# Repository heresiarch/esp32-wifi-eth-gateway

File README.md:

# esp32-wifi-eth-gateway
Proof-of-concept Wifi ⇄ Ethernet gateway running on an ESP32-C6.

## Hardware
- Waveshare ESP32-C6-Zero (or compatible ESP32-C6)
- WIZnet W5500 SPI Ethernet module (or compatible SPI Ethernet adapter)

## Project summary
This project implements a network gateway that forwards traffic between the ESP32's Wi‑Fi interface and a SPI‑based Ethernet interface. It can be used to bridge devices on an Ethernet subnet onto a Wi‑Fi network (or vice versa) for testing, prototyping, and embedded networking research. The implementation uses ESP-IDF networking components and the W5500 driver included as a component.

## Features
- Bridge packets between Wi‑Fi and Ethernet interfaces
- Uses ESP‑IDF networking stack
- Configurable via `menuconfig` / `sdkconfig`
- Example application code in `main/` (`main.c`, `proxy.c`)
- Wifi runs as DHCP client
- Ethernet run as DHCP Server
- TCP proxy on port 8888, plus an optional second independent proxy (default port 502 for Modbus TCP) that can be switched on or off with `SECOND_PROXY_ENABLE`, each with its own target

## Repository layout
- `main/` — application source and component Kconfig
- `partition_table/`, `sdkconfig*` — project configuration
- `managed_components/` — included external components (W5500, ethernet init, etc.)
- `build/` — build output (ignored by source control)
- `circuit-design` KiCad 9 project

## Requirements
- ESP-IDF (supported version: refer to the `esp-idf/` subfolder or `CMakeLists.txt`)
- A toolchain for the target (e.g. for ESP32‑C6)
- `idf.py` (part of ESP‑IDF)

## Quick build & flash
1. Set up ESP‑IDF and toolchain, then source the environment (example):

```bash
. $HOME/esp/esp-idf/export.sh
```

2. (Optional) set the target if needed:

```bash
idf.py set-target esp32c6
```

3. Create `main/Kconfig.projbuild` from the template (see "Create your own configuration") and configure project options (wifi credentials, ethernet pins, etc.):

```bash
idf.py menuconfig
```

4. Build, flash and monitor:

```bash
idf.py build
idf.py -p /dev/ttyUSB0 flash monitor
```

Replace `/dev/ttyUSB0` with your serial device.

## Create your own configuration
The project settings (Wi-Fi credentials, Ethernet addressing, proxy ports and targets) are defined in `main/Kconfig.projbuild`. That file is listed in `.gitignore`, so your credentials stay out of the repository. The repository only contains the template `main/Kconfig.projbuild.example`. Before the first build, create your own file from it:

1. Copy the template:

```bash
cp main/Kconfig.projbuild.example main/Kconfig.projbuild
```

2. (Optional) edit the `default` values in `main/Kconfig.projbuild`, for example `WIFI_SSID`, `WIFI_PASSWORD`, `ETHERNET_IP` and the proxy targets. You can also leave the defaults and set everything in step 3.

3. Open menuconfig and check or change the values under "Project Network Configuration":

```bash
idf.py menuconfig
```

   - "Wi-Fi Settings": `WIFI_SSID`, `WIFI_PASSWORD`
   - "Ethernet & Proxy Settings": Ethernet IP, netmask and gateway, the first proxy, and the optional second proxy (`SECOND_PROXY_ENABLE`)

4. Build and flash as described in "Quick build & flash".

Notes:
- Without `main/Kconfig.projbuild` the `CONFIG_*` options used by `main.c` are missing and the build fails.
- Values you set in menuconfig are stored in `sdkconfig`, which takes priority over the `default` values in `Kconfig.projbuild`. If you change a `default` later and the old value is still used, change it in menuconfig, or delete `sdkconfig` and run `idf.py reconfigure`. Note that deleting `sdkconfig` resets all of your settings.
- If you add or rename options in `main/Kconfig.projbuild`, run `idf.py reconfigure` so `sdkconfig` picks them up.
- When the template changes in the repository (new options), compare it with your copy, for example with `diff main/Kconfig.projbuild.example main/Kconfig.projbuild`, and add the new options to your file.
- Do not commit `main/Kconfig.projbuild` or `sdkconfig` if they contain real passwords.

## Configuration notes
- Wi‑Fi credentials and runtime options can be set in `menuconfig` or stored in `sdkconfig`/`sdkconfig.defaults` depending on how the project exposes them.
- Hardware pin mappings for the SPI Ethernet module are configured in `menuconfig` or in the ethernet component source — check `managed_components/espressif__w5500/` for driver-specific settings.

## Proxy configuration
The firmware runs two independent TCP proxy instances. Each one listens on its own port and forwards traffic to its own target. Both are set in `idf.py menuconfig` under "Ethernet & Proxy Settings":

| Option | Default | Purpose |
|---|---|---|
| `SERVER_LISTEN_PORT` | 8888 | Listen port of the first proxy |
| `PROXY_TARGET_ADDRESS` | 10.0.0.2 | Target IP or host of the first proxy |
| `PROXY_TARGET_PORT` | 8888 | Target port of the first proxy |
| `SECOND_PROXY_ENABLE` | y | Switch that enables the second proxy |
| `SECOND_SERVER_LISTEN_PORT` | 502 | Listen port of the second proxy (Modbus TCP) |
| `SECOND_PROXY_TARGET_ADDRESS` | 10.0.0.2 | Target IP or host of the second proxy |
| `SECOND_PROXY_TARGET_PORT` | 502 | Target port of the second proxy |

Notes:
- The second proxy is optional. `SECOND_PROXY_ENABLE` defaults to `y`. The three options `SECOND_SERVER_LISTEN_PORT` (502), `SECOND_PROXY_TARGET_ADDRESS` (10.0.0.2) and `SECOND_PROXY_TARGET_PORT` (502) are visible in `menuconfig` only when the switch is set. When it is unset, only the first proxy is started and the second-port checks are skipped.
- Ports must be in the range 1 to 65535.
- The two listen ports must differ. With `SECOND_PROXY_ENABLE` set, the build fails with a compile-time error if they are equal or out of range. With it unset, only the first port is checked.
- Each proxy serves one client at a time. The two proxies run in parallel and do not affect each other.
- Log lines are prefixed with `[port N]` so you can tell the two proxies apart.
- `main/Kconfig.projbuild.example` is a template with placeholder values. See "Create your own configuration" for how to copy it to `main/Kconfig.projbuild`.

## Wiring (ESP32 → W5500)
Below are the SPI pin assignments used in this project.

| Signal | ESP32-C6 pin | W5500 pin | Direction | Kconfig option |
|---|---|---|---|---|
| SCLK | GPIO4 | SCLK | ESP32 → W5500 | `CONFIG_ETHERNET_SPI_SCLK_GPIO=4` |
| MOSI | GPIO5 | MOSI | ESP32 → W5500 | `CONFIG_ETHERNET_SPI_MOSI_GPIO=5` |
| MISO | GPIO2 | MISO | W5500 → ESP32 | `CONFIG_ETHERNET_SPI_MISO_GPIO=2` |
| CS (CS0) | GPIO3 | SCS | ESP32 → W5500 | `CONFIG_ETHERNET_SPI_CS0_GPIO=3` |
| INT | GPIO15 | INT | W5500 → ESP32 | `CONFIG_ETHERNET_SPI_INT0_GPIO=15` |
| PHY_RST | GPIO14 | RESET | ESP32 → W5500 | `CONFIG_ETHERNET_SPI_PHY_RST0_GPIO=14` |

**Architecture**

- **Overview:** The ESP32 runs a small application that bridges packets between the Wi‑Fi stack (`esp_wifi` / `lwIP`) and a SPI Ethernet controller (W5500). The user-space TCP proxy (`proxy.c`) accepts connections on the ESP32 and forwards bytes between the two interfaces.

- **Responsibilities:**
	- `main.c` — initialises Wi‑Fi, Ethernet and starts the first proxy instance and, if `SECOND_PROXY_ENABLE` is set, the second one.
	- `proxy.c` — accepts TCP connections and forwards traffic between endpoints. `proxy_start()` is called once per enabled port.
	- `status_led.c` — indicates general on status and traffic activity (Ethernet/Wi‑Fi).

Architecture diagram:

```mermaid
flowchart TD
    WIFI(["Wi-Fi network"])
    DEV(["Local devices"])
    W5500["W5500 Ethernet controller"]

    subgraph ESP["ESP32-C6"]
        STA["esp_wifi STA<br/>DHCP client"]
        P1["proxy.c: port 8888<br/>task + buffer"]
        P2["proxy.c: port 502<br/>task + buffer, optional"]
        ETH["esp_eth SPI driver"]
        DHCPS["DHCP server"]
        LED["status_led.c"]
    end

    WIFI <--> STA
    STA <--> P1
    STA <--> P2
    P1 <--> ETH
    P2 <--> ETH
    DHCPS --- ETH
    ETH <-->|SPI| W5500
    W5500 <--> DEV
```

Note: If you change these pins via `menuconfig`, update `sdkconfig` and re-flash the firmware so the driver uses the new assignments.

## Circuit Design
I create a KiCad 9 project with some custom footprints for the following components I used `circuit-design`:
* Waveshare ESP32-C6-Zero with headers
* TPS2553 USB eFuse on DIP-6 Adapter (Powerlimit 400mA)
* Wiznet 5500 module with headers
* generic USB-C Header which included termination resistors

## License & contributors
See the `LICENSE` file for license details. Contributions and issues are welcome.

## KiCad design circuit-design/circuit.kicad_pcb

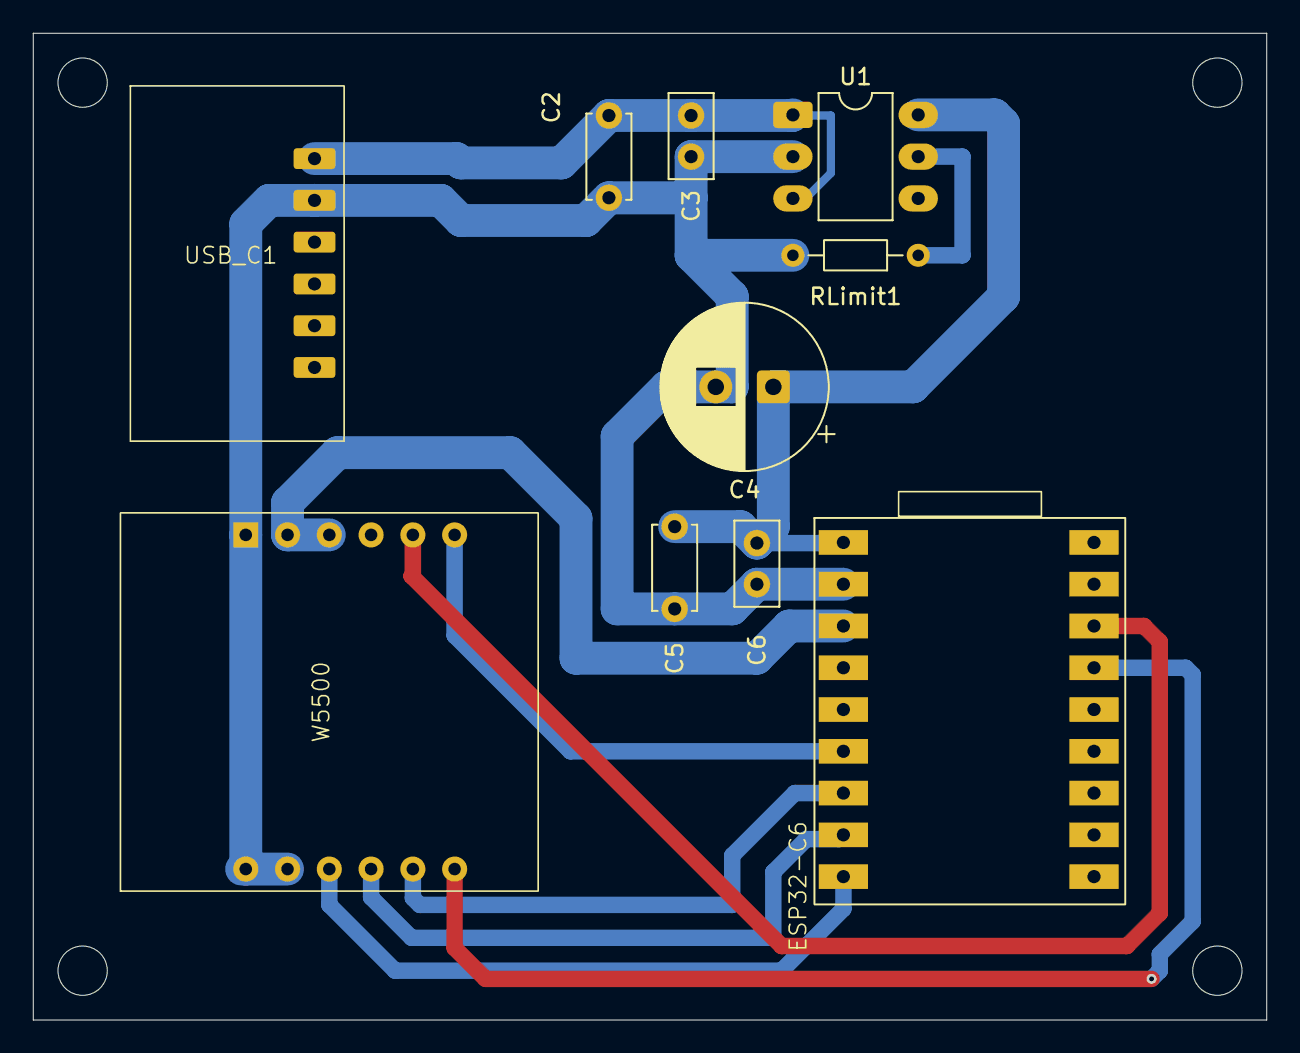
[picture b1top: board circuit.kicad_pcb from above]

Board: 2 copper layers, 75.0 x 60.0 mm, 10 parts (0 on the bottom side), 11 nets.

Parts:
C2, C5: 1uF/10V; C_Disc_D5.0mm_W2.5mm_P5.00mm
C3, C6: 100nF; C_Disc_D5.0mm_W2.5mm_P2.50mm
C4: 1000uF/10V; CP_Radial_D10.0mm_P3.50mm
ESP32-C6: Waveshare-ESP32-C6-Zero
RLimit1: 67k; R_Axial_DIN0204_L3.6mm_D1.6mm_P7.62mm_Horizontal
U1: TPS2553; DIP-6_W7.62mm_LongPads
USB_C1: USB-C-Plug
W5500: w5500-eth-breakout

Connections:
GND: C2.2, C3.2, C4.2, C5.2, C6.2, ESP32-C6.2 (GND), RLimit1.2, U1.2 (GND), USB_C1.2 (GND), W5500.1 (GND), W5500.2 (GND), W5500.12 (GND)
INTn: ESP32-C6.15 (IO15), W5500.6 (INTn)
MISO: ESP32-C6.6 (IO2), W5500.7 (MISO)
MOSI: ESP32-C6.9 (IO5), W5500.3 (MOSI)
unnamed: ESP32-C6.3 (V3V), W5500.10 (3,3V), W5500.11 (3,3V)
unnamed: C4.1, C5.1, C6.1, ESP32-C6.1 (VCC), U1.6 (OUT)
unnamed: C2.1, C3.1, U1.1 (IN), U1.3 (EN), USB_C1.1 (VBUS)
unnamed: RLimit1.1, U1.5 (ILIM)
RSTn: ESP32-C6.16 (IO14), W5500.8 (RSTn)
SCLK: ESP32-C6.8 (IO4), W5500.4 (SCLK)
SCNn: ESP32-C6.7 (IO3), W5500.5 (SCNn)
